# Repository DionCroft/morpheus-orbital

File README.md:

# Morpheus ORBITAL

**A six-layer KiCad prototype for a portable 7.3-inch colour e-paper device.**

Morpheus ORBITAL connects an Espressif **ESP32-S3-WROOM-1-N16R8** to a Good Display **GDEP073E01** colour e-paper panel. It adds USB-C, microSD, a Bosch **BME690** environmental sensor, and a single-cell battery power path. The board keeps the USB-C port, card slot and buttons along the edges and reserves space for the display flex and the module antenna.

[Download the prototype ZIP](https://github.com/DionCroft/morpheus-orbital/releases/download/v0.1.0-prototype/Morpheus-ORBITAL-v0.1.0-prototype.zip) · [Download the 18-sheet schematic PDF](docs/Morpheus-Schematic.pdf) · [Open in KiCad](#open-in-kicad) · [Find a component](#component-index) · [Download BOM CSV](Morpheus-BOM.csv) · [Populated STEP](docs/Morpheus-assembled.step) · [JLCPCB and bring-up checklist](docs/PROTOTYPE_CHECKLIST.md)

<p align="center">
  
</p>

*Component side shown upright. The USB-C port and microSD socket are on the left, and the display FPC is along the bottom.*

## Hardware at a glance

| Function | Main components |
| --- | --- |
| Compute and wireless | Espressif **ESP32-S3-WROOM-1-N16R8** |
| Display | Good Display **GDEP073E01** 7.3-inch colour e-paper panel and Hirose **FH34SRJ-50S-0.5SH(50)** 50-pin display connector |
| Environmental sensing | Bosch Sensortec **BME690** gas, humidity, pressure and temperature sensor |
| USB-C and protection | GCT **USB4085-GF-A**, onsemi **FUSB303BTMX** Type-C controller, and TI **TPD4E1U06DCKR** ESD protection |
| Storage | Hirose **DM3AT-SF-PEJM5** microSD socket |
| Battery and regulation | TI **BQ25616RTWR** charger, **BQ27441DRZR-G1A** fuel gauge, and **TPS63020DSJR** buck-boost converter |
| Temperature monitoring and controls | TI **ADS1115IDGSR** ADC, external thermistor headers, and **K2-1102SP-A4SC-04** boot and refresh switches |

## Open in KiCad

1. Install [KiCad 10](https://www.kicad.org/download/), including its standard libraries. The project was reviewed with KiCad **10.0.4**. Install the standard KiCad 3D model library for the complete assembly view.
2. Clone the repository below, or use [Download ZIP](https://github.com/DionCroft/morpheus-orbital/archive/refs/heads/main.zip) and extract the entire archive. The project uses relative library and model paths.

       git clone https://github.com/DionCroft/morpheus-orbital.git

3. From KiCad's project manager, open [circuit_design/Morpheus/Morpheus.kicad_pro](circuit_design/Morpheus/Morpheus.kicad_pro). Open **Schematic Editor** or **PCB Editor** from the project.
4. In PCB Editor, choose **View > 3D Viewer** to inspect the populated board. The display panel, battery, and external probes are separate from the PCB assembly.

## Mechanical model

The [populated STEP assembly](docs/Morpheus-assembled.step) contains the board and all **164 fitted components**. It is intended for CAD viewing and enclosure planning. Some component bodies use drawing-based envelopes, so check final fit against the actual mating parts.

## Rear 3D view

<p align="center">
  
</p>

## Component index

Every distinct manufacturer part number in the [reference BOM](Morpheus-BOM.csv) is listed below. The **61 part numbers** cover **169 schematic references**, including the off-board display and four DNP (do not populate) positions. The routed PCB has 164 fitted components. NT901 is the copper net tie.

### Processing, power and semiconductors

| Exact part number | Component or value | Manufacturer | References |
| --- | --- | --- | --- |
| `ADS1115IDGSR` | ADS1115 16-bit ADC | Texas Instruments | U702 |
| `BME690` | Gas, humidity, pressure and temperature sensor | Bosch Sensortec | U3 |
| `BQ25616RTWR` | BQ25616 single-cell battery charger with power path | Texas Instruments | U901 |
| `BQ27441DRZR-G1A` | BQ27441-G1A battery fuel gauge | Texas Instruments | U701 |
| `BZT52C27` | 27 V Zener diode | Jiangsu Changjing Electronics Technology | D3 |
| `ESP32-S3-WROOM-1-N16R8` | ESP32-S3 Wi-Fi and Bluetooth LE MCU module | Espressif Systems | U1 |
| `FUSB303BTMX` | FUSB303B USB Type-C port controller | onsemi | U802 |
| `KT-0805G` | Green indicator LED | Hubei KENTO Electronics | D4, D5 |
| `MBR0530T1G` | Schottky rectifier | onsemi | D2, D6, D7, D8 |
| `SI2301CDS` | P-channel MOSFET | TECH PUBLIC | Q9 |
| `SN74HCS08PWR` | Quad Schmitt-trigger AND gate | Texas Instruments | U1603 |
| `SN74LVC1G14DBVR` | Single Schmitt-trigger inverter | Texas Instruments | U803, U1601, U1602 |
| `Si1308EDL-T1-GE3` | N-channel MOSFET | Vishay | Q8 |
| `TPD4E1U06DCKR` | TPD4E1U06 four-channel ESD protection | Texas Instruments | D1 |
| `TPS2553DBVR` | TPS2553 current-limited power switch | Texas Instruments | U805 |
| `TPS389001DSET` | TPS3890 adjustable voltage supervisor | Texas Instruments | U1701 |
| `TPS389030DSET` | TPS3890 fixed-threshold voltage supervisor | Texas Instruments | U804, U806 |
| `TPS63020DSJR` | TPS63020 buck-boost converter | Texas Instruments | U807 |
| `TPS70933DBVR` | TPS70933 3.3 V LDO regulator | Texas Instruments | U801 |

### Display, connectors and switches

| Exact part number | Component or value | Manufacturer | References |
| --- | --- | --- | --- |
| `2.0-2P WT` | Two-position 2.0 mm battery connector | SHOU HAN | J2 |
| `DM3AT-SF-PEJM5` | microSD card socket | Hirose Electric | J4 |
| `FH34SRJ-50S-0.5SH(50)` | 50-position 0.5 mm display FPC connector | Hirose | J3 |
| `GDEP073E01` | 7.3-inch colour e-paper panel | Good Display | U5 (off-board) |
| `K2-1102SP-A4SC-04` | Boot and refresh tactile switch | Korean Hroparts Electronics | SW1, SW2 |
| `M20-9990246` | 2.54 mm header for temperature sense or charge disable | Harwin | J602, J603, J702 |
| `USB4085-GF-A` | USB-C receptacle | GCT | J1 |

### Capacitors and inductors

| Exact part number | Component or value | Manufacturer | References |
| --- | --- | --- | --- |
| `CL10B104KB8NNNC` | 100nF ceramic capacitor | Samsung Electro-Mechanics | C21, C22, C32, C34, C52, C54, C59, C61, C64, C69, C703, C704, C803, C804, C805, C808, C811, C1601, C1602, C1603, C1701 |
| `CL10B473KB8NNNC` | 47nF/50V ceramic capacitor | Samsung Electro-Mechanics | C904 |
| `CL21B105KBFNNNE` | 1uF ceramic capacitor | Samsung Electro-Mechanics | C23, C24, C33, C41, C42, C43, C44, C45, C46, C47 (DNP), C53, C701, C801, C806, C901 |
| `CL21B224KBFNNNE` | 220nF/50V ceramic capacitor | Samsung Electro-Mechanics | C816, C817 |
| `CL21B474KBFNNNE` | 470nF/50V ceramic capacitor | Samsung Electro-Mechanics | C55, C68, C702 |
| `CL31B225KBHNNNE` | 2.2uF/50V ceramic capacitor | Samsung Electro-Mechanics | C40 |
| `CL31B475KBHNNNE` | 4.7uF/50V ceramic capacitor | Samsung Electro-Mechanics | C56, C62, C67, C802, C903 |
| `CL32B106KBJNNNE` | 10uF ceramic capacitor | Samsung Electro-Mechanics | C31, C35, C48, C49, C50, C51, C57, C58, C60, C63, C65, C66, C807, C809, C810, C902, C905, C906, C907, C908 |
| `CL32B226KAJNNNE` | 22uF/25V ceramic capacitor | Samsung Electro-Mechanics | C812, C813, C814 |
| `GRM1555C1H102JA01D` | 1nF/50V ceramic capacitor (C0G) | Murata | C90 |
| `LQH32PN100MNCL` | 10 uH inductor | Murata | L3, L4 |
| `XAL5030-102MEC` | 1 uH power inductor | Coilcraft | L901 |
| `XGL4020-152MEC` | 1.5 uH power inductor | Coilcraft | L801 |

### Resistors and current sense

| Exact part number | Component or value | Manufacturer | References |
| --- | --- | --- | --- |
| `CRF1206-FZ-R010ELF` | 10 mOhm current-sense resistor | Bourns | R701 |
| `CRM1206-FX-R220ELF` | 0.22 Ohm current-sense resistor | Bourns | R28, R30 |
| `ERA3AEB1022V` | 10.2k resistor | Panasonic Industry | R1702 |
| `ERA3AEB184V` | 180k resistor | Panasonic Industry | R811 |
| `ERA3AEB303V` | 30k resistor | Panasonic Industry | R1701 |
| `RC0603FR-07100KL` | 100k resistor | Yageo | R24 (DNP), R1703 |
| `RC0603FR-0710KL` | 10k resistor | Yageo | R12, R13, R21, R605, R702, R703, R706, R708, R709, R802, R813, R814, R815, R902, R1001, R1002, R1003, R1004, R1005 |
| `RC0603FR-071K5L` | 1.5k resistor | Yageo | R901 |
| `RC0603FR-071KL` | 1k resistor | Yageo | R707 |
| `RC0603FR-071ML` | 1M resistor | Yageo | R27, R29, R704, R705, R809 |
| `RC0603FR-0722KL` | 22k resistor | Yageo | R806 |
| `RC0603FR-07249KL` | 249k resistor | Yageo | R805 |
| `RC0603FR-072K2L` | 2.2k resistor | Yageo | R710, R711, R1006, R1007 |
| `RC0603FR-07300KL` | 300k resistor | Yageo | R804 |
| `RC0603FR-0746K4L` | 46.4k resistor | Yageo | R602 |
| `RC0603FR-07470KL` | 470k resistor | Yageo | R808 |
| `RC0603FR-0747KL` | 47k resistor | Yageo | R23 (DNP) |
| `RC0603FR-07510RL` | 510 Ohm resistor | Yageo | R14, R15, R903 |
| `RC0603FR-075K9L` | 5.9k resistor | Yageo | R601 |
| `RC0603JR-070RL` | 0R jumper resistor | Yageo | R25, R26, R31 (DNP), R32, R33, R34, R801 |
| `RC1206FR-07220RL` | 220R resistor | Yageo | R812 |
| `RT0603BRD071ML` | 1M resistor | Yageo | R810 |

## Prototype and reuse

Use the [JLCPCB ordering and first-board bring-up checklist](docs/PROTOTYPE_CHECKLIST.md) to plan a prototype order and record the bench results.

This is a reviewed CAD prototype. The full PCB DRC recorded zero unconnected items, three warnings and 50 reviewed footprint-parity records. Hardware qualification is open for USB impedance on the finished stackup, selective filled and capped vias, display bias and startup, battery and thermistor behaviour, display connector fit, RF performance, and assembly clearances. Verify those items against the actual parts and fabrication process before building.

The original hardware design is licensed under [CERN-OHL-S-2.0](LICENSES/CERN-OHL-S-2.0.txt). The source location is [this repository](https://github.com/DionCroft/morpheus-orbital). The crest artwork and personal signature retain separate terms. KiCad library material retains its upstream license. [Third-party and artwork notices](THIRD_PARTY_NOTICES.md).

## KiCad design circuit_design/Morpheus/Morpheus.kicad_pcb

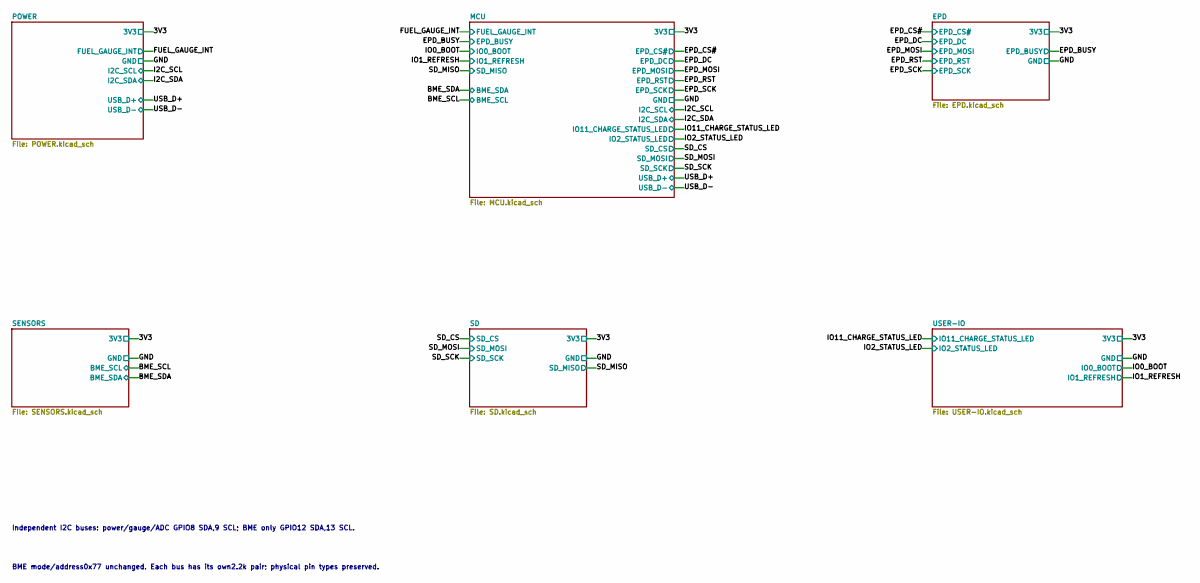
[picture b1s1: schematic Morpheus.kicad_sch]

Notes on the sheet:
Independent I2C buses: power/gauge/ADC GPIO8 SDA,9 SCL; BME only GPIO12 SDA,13 SCL.
BME mode/address0x77 unchanged. Each bus has its own2.2k pair; physical pin types preserved.

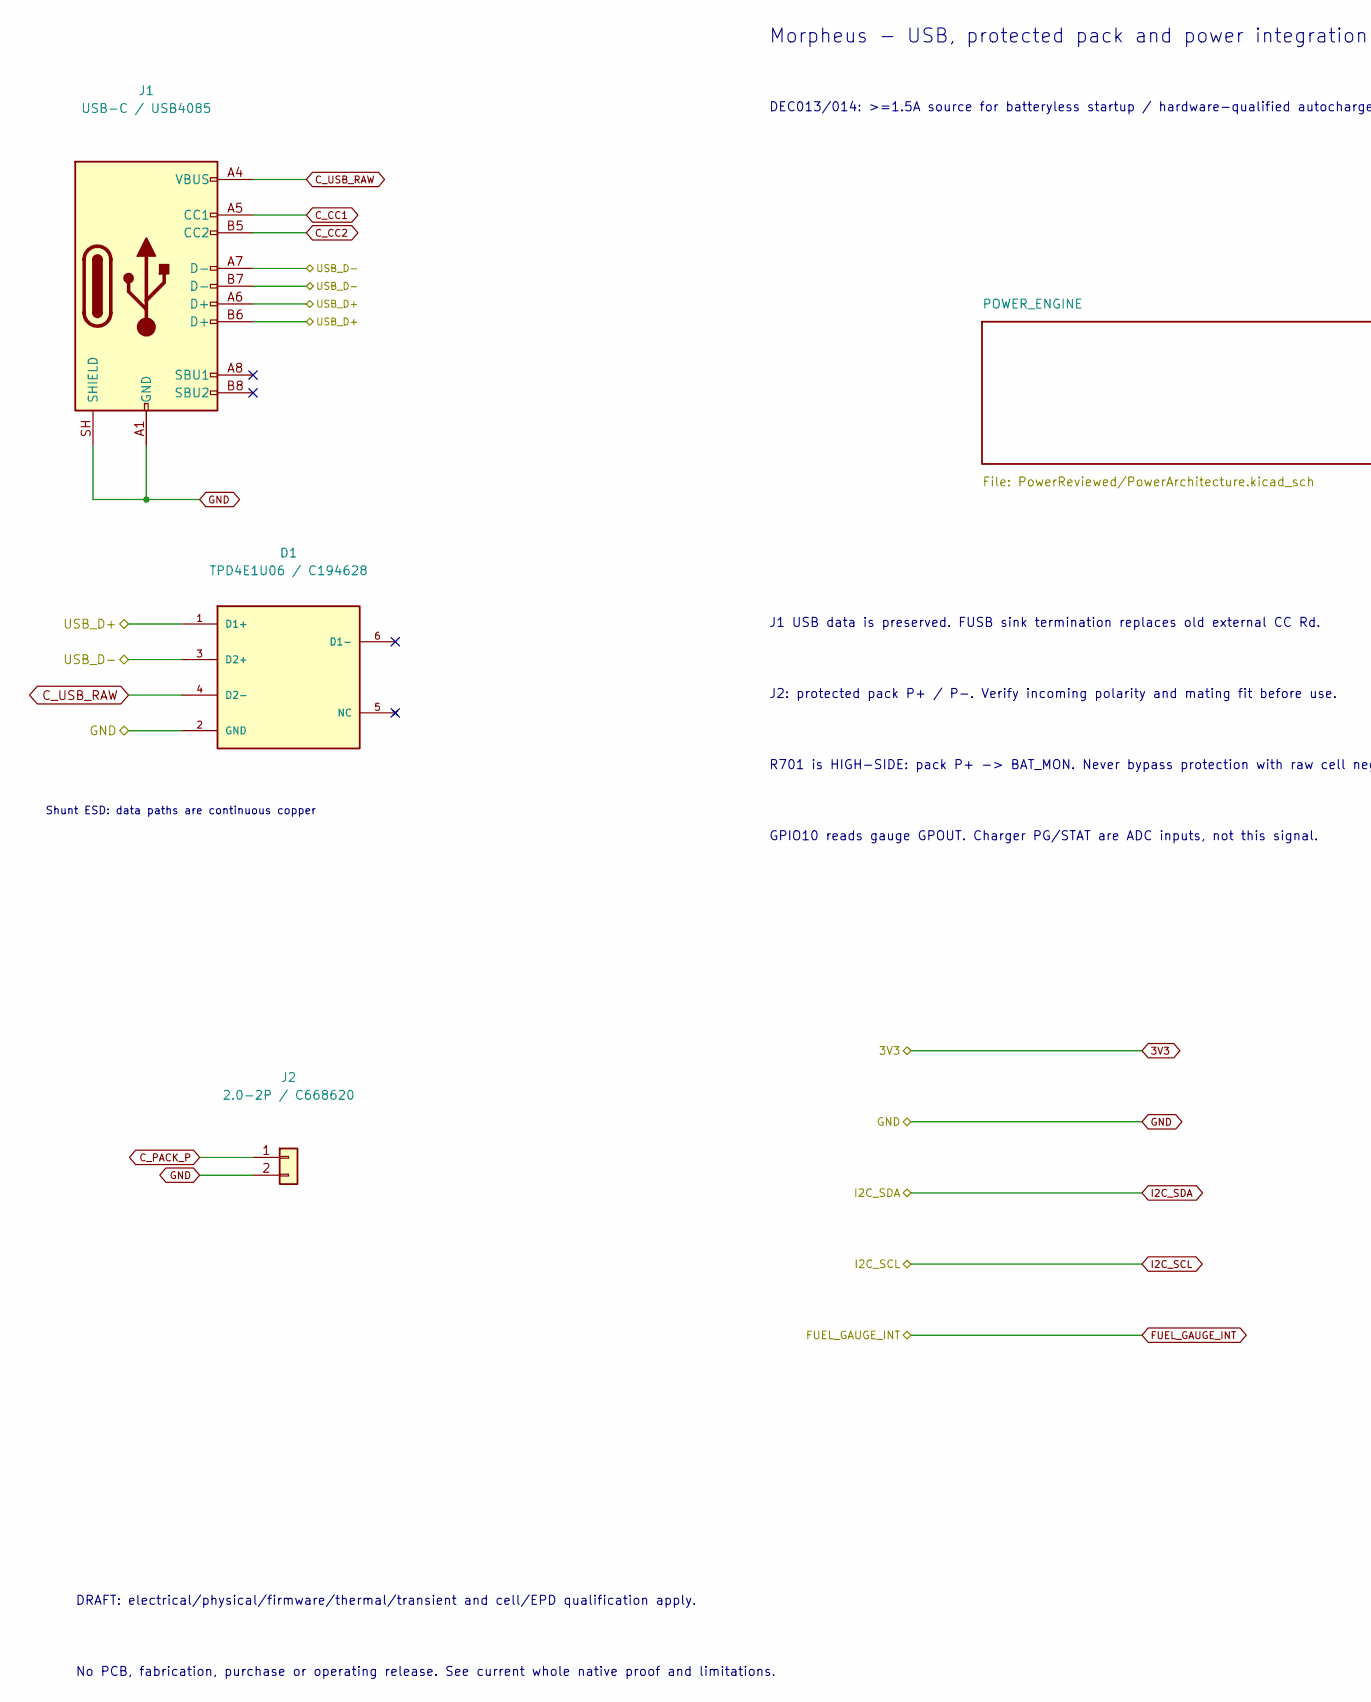
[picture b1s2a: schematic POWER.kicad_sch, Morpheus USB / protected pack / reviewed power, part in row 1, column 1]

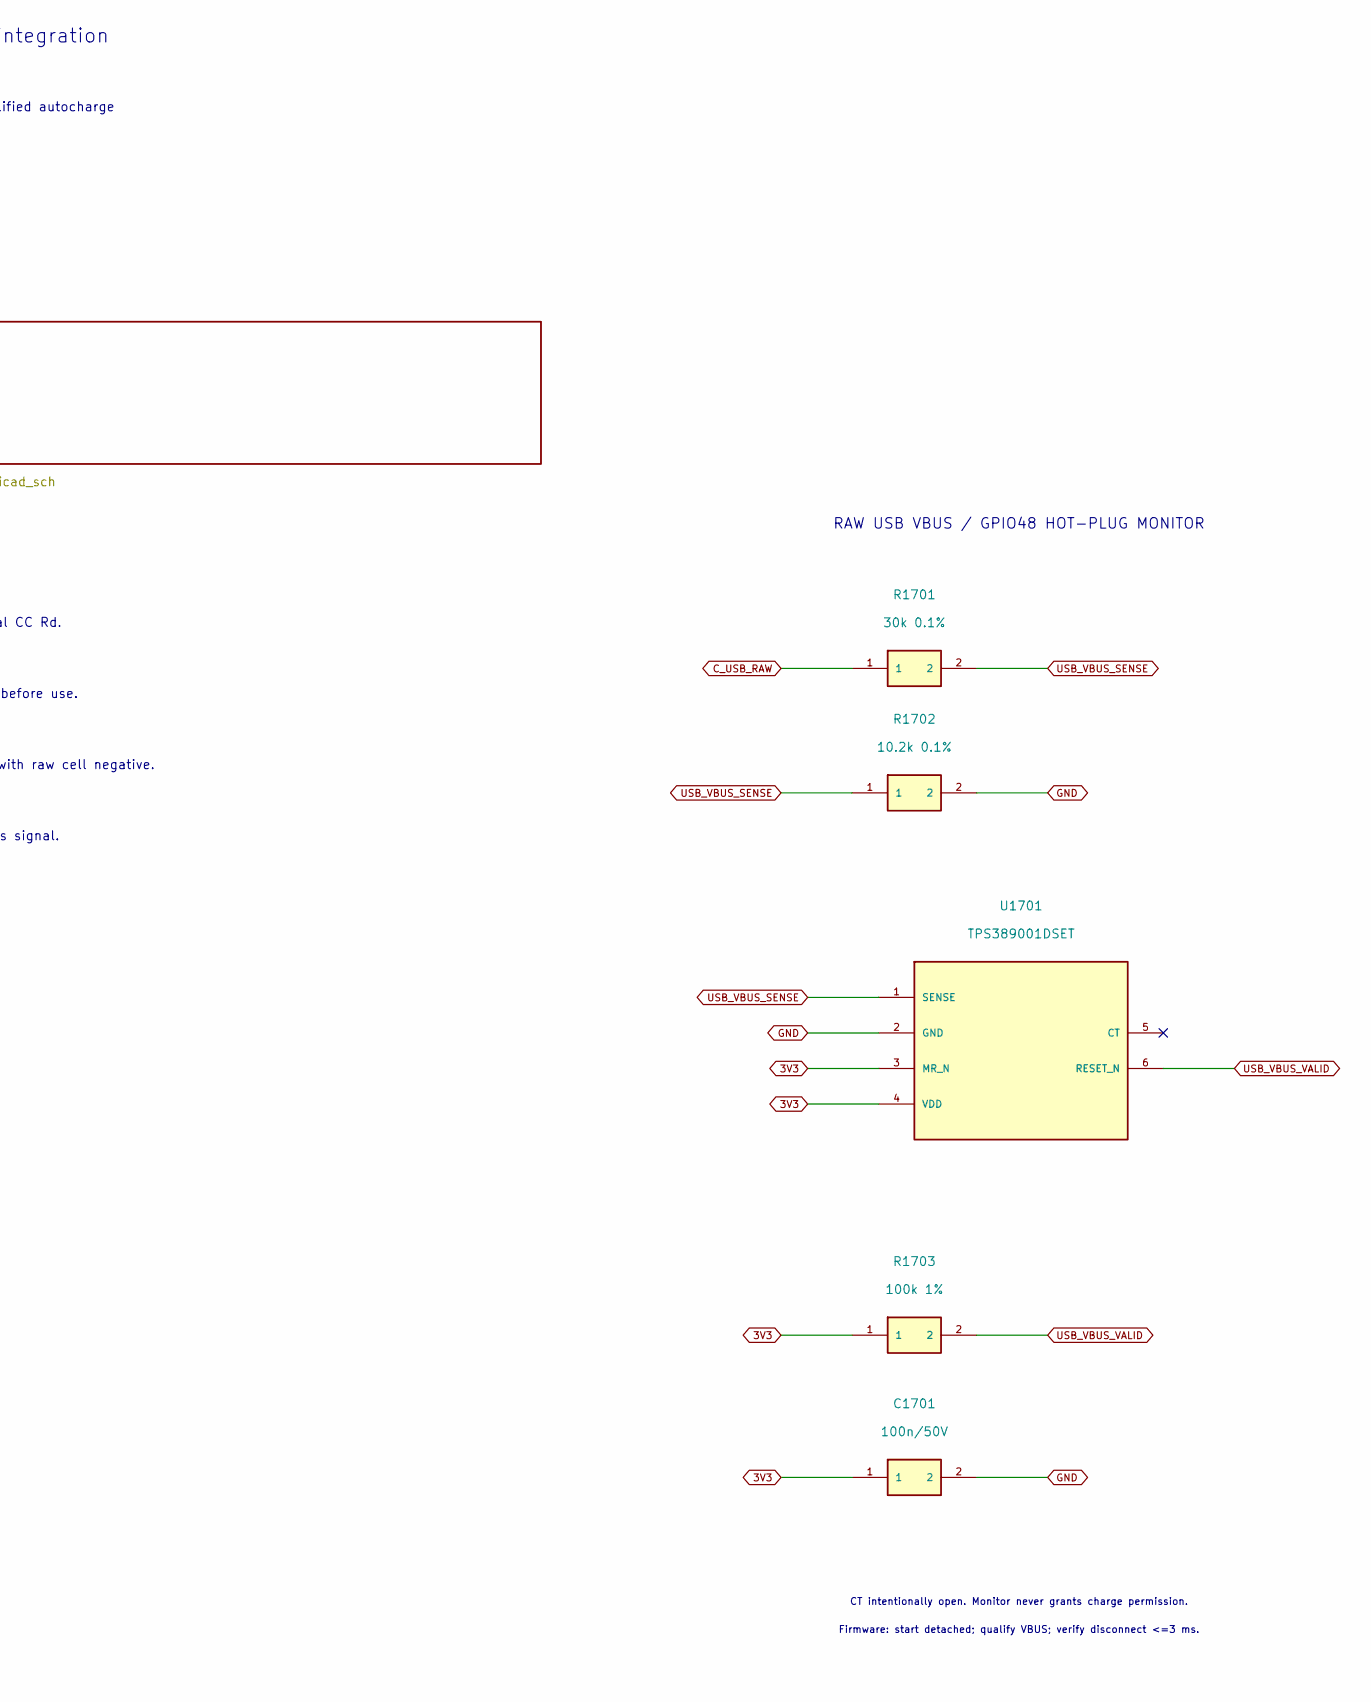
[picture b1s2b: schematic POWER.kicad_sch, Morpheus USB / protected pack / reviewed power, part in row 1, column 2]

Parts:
C1701: 100n/50V; Samsung_C0603; ManufacturerPartNumber CL10B104KB8NNNC
D1: TPD4E1U06 / C194628; TI_TPD4E1U06_DCK0006A; ManufacturerPartNumber TPD4E1U06DCKR; LCSC C194628
J1: USB-C / USB4085; USB_C_Receptacle_GCT_USB4085_GF_A; ManufacturerPartNumber USB4085-GF-A
J2: 2.0-2P / C668620; SHOU_HAN_2_0_2P_WT; ManufacturerPartNumber 2.0-2P WT; LCSC C668620
R1701: 30k 0.1%; Panasonic_ERA3A; ManufacturerPartNumber ERA3AEB303V
R1702: 10.2k 0.1%; Panasonic_ERA3A; ManufacturerPartNumber ERA3AEB1022V
R1703: 100k 1%; R_0603_1608Metric; ManufacturerPartNumber RC0603FR-07100KL
U1701: TPS389001DSET; TI_DSE0006A; ManufacturerPartNumber TPS389001DSET

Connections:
3V3: C1701.1, R1703.1, U1701.3 (MR_N), U1701.4 (VDD); also elsewhere on the board
/USB_D+: D1.1 (D1+), J1.A6 (D+), J1.B6 (D+); also elsewhere on the board
/USB_D-: D1.3 (D2+), J1.A7 (D-), J1.B7 (D-); also elsewhere on the board
C_CC1: J1.A5 (CC1); also elsewhere on the board
C_CC2: J1.B5 (CC2); also elsewhere on the board
C_PACK_P: J2.1; also elsewhere on the board
C_USB_RAW: D1.4 (D2-), J1.A4 (VBUS), J1.A9 (VBUS), J1.B4 (VBUS), J1.B9 (VBUS), R1701.1; also elsewhere on the board
GND: C1701.2, D1.2 (GND), J1.A1 (GND), J1.A12 (GND), J1.B1 (GND), J1.B12 (GND), J1.SH (SHIELD), J2.2, R1702.2, U1701.2 (GND); also elsewhere on the board
USB_VBUS_SENSE: R1701.2, R1702.1, U1701.1 (SENSE)
USB_VBUS_VALID: R1703.2, U1701.6 (RESET_N); also elsewhere on the board

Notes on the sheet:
Shunt ESD: data paths are continuous copper
Morpheus - USB, protected pack and power integration
DEC013/014: >=1.5A source for batteryless startup / hardware-qualified autocharge
J1 USB data is preserved. FUSB sink termination replaces old external CC Rd.
J2: protected pack P+ / P-. Verify incoming polarity and mating fit before use.
R701 is HIGH-SIDE: pack P+ -> BAT_MON. Never bypass protection with raw cell negative.
GPIO10 reads gauge GPOUT. Charger PG/STAT are ADC inputs, not this signal.
DRAFT: electrical/physical/firmware/thermal/transient and cell/EPD qualification apply.
No PCB, fabrication, purchase or operating release. See current whole native proof and limitations.
RAW USB VBUS / GPIO48 HOT-PLUG MONITOR
CT intentionally open. Monitor never grants charge permission.
Firmware: start detached; qualify VBUS; verify disconnect <=3 ms.

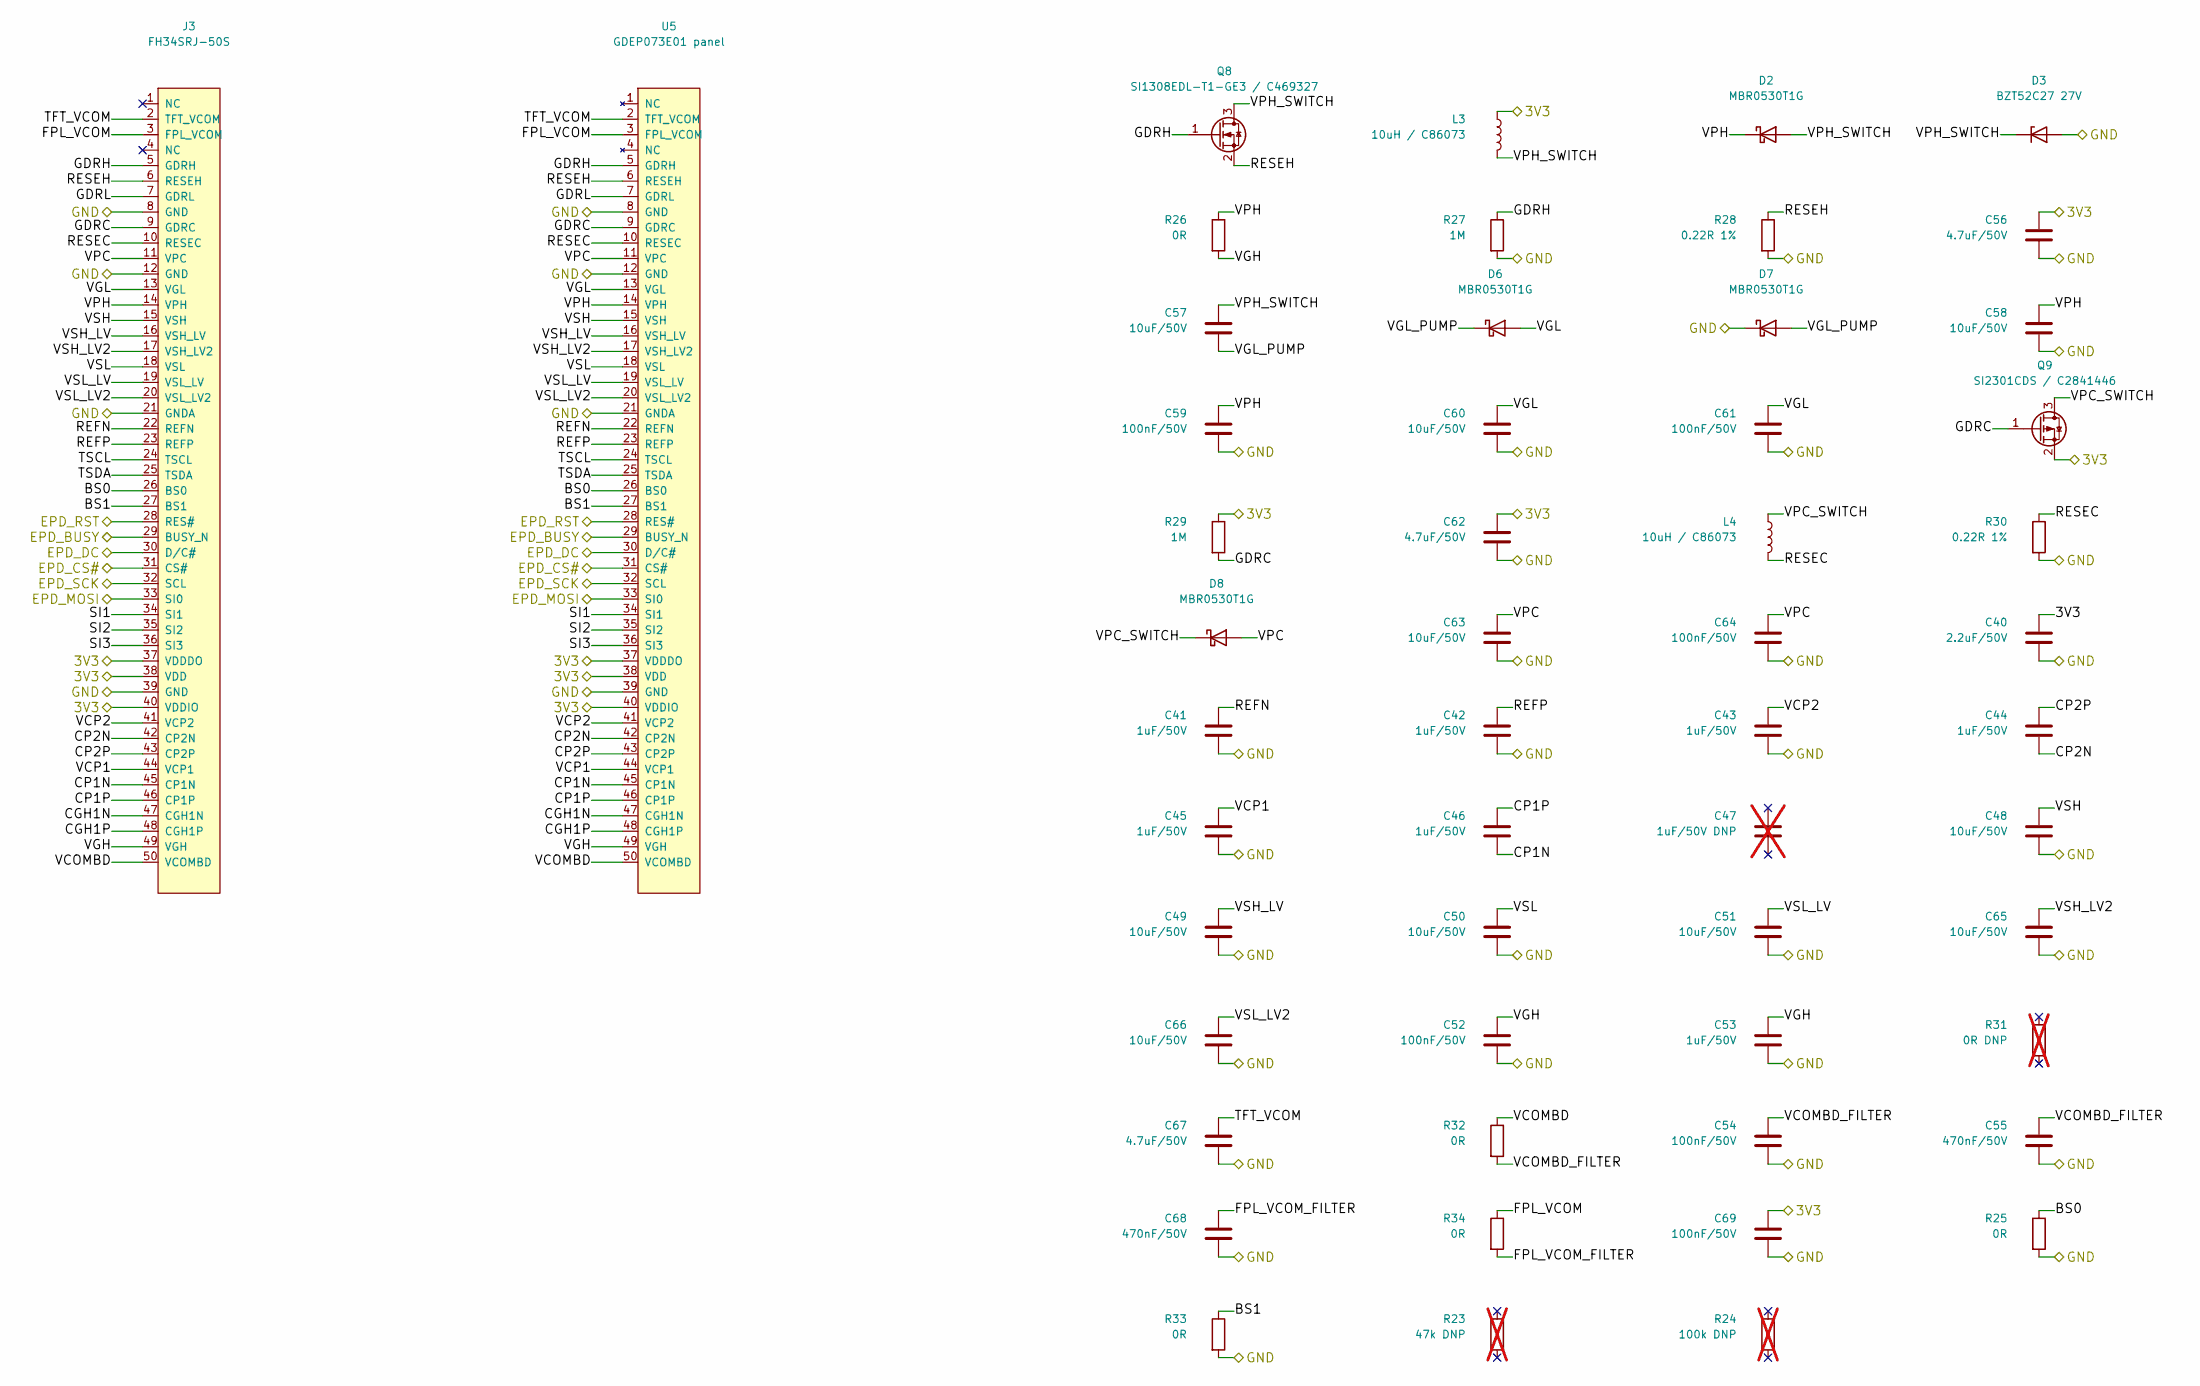
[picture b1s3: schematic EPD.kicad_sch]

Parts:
C40: 2.2uF/50V; Samsung_C1206; ManufacturerPartNumber CL31B225KBHNNNE
C41, C42, C43, C44, C45, C46, C53: 1uF/50V; Samsung_C0805; ManufacturerPartNumber CL21B105KBFNNNE
C47: 1uF/50V DNP; Samsung_C0805; ManufacturerPartNumber CL21B105KBFNNNE; not fitted
C48, C49, C50, C51, C57, C58, C60, C63, C65, C66: 10uF/50V; Samsung_C1210; ManufacturerPartNumber CL32B106KBJNNNE; LCSC C138687
C52, C54, C59, C61, C64, C69: 100nF/50V; Samsung_C0603; ManufacturerPartNumber CL10B104KB8NNNC
C55, C68: 470nF/50V; Samsung_C0805; ManufacturerPartNumber CL21B474KBFNNNE
C56, C62, C67: 4.7uF/50V; Samsung_C1206; ManufacturerPartNumber CL31B475KBHNNNE
D2, D6, D7, D8: MBR0530T1G; onsemi_MBR0530_SOD123; ManufacturerPartNumber MBR0530T1G; LCSC C82046
D3: BZT52C27 27V; JSCJ_BZT52C_SOD123; ManufacturerPartNumber BZT52C27; LCSC C81935
J3: FH34SRJ-50S; Hirose_FH34SRJ_50S_0_5SH_50_Primary; ManufacturerPartNumber FH34SRJ-50S-0.5SH(50)
L3, L4: 10uH / C86073; L_Murata_LQH32PN100MNCL; ManufacturerPartNumber LQH32PN100MNCL; LCSC C86073
Q8: SI1308EDL-T1-GE3 / C469327; SOT323_Vishay_Si1308EDL; ManufacturerPartNumber Si1308EDL-T1-GE3; LCSC C469327
Q9: SI2301CDS / C2841446; TECH_PUBLIC_SI2301CDS_Physical_GSD; ManufacturerPartNumber SI2301CDS; LCSC C2841446
R23: 47k DNP; R_0603_1608Metric; ManufacturerPartNumber RC0603FR-0747KL; not fitted
R24: 100k DNP; R_0603_1608Metric; ManufacturerPartNumber RC0603FR-07100KL; not fitted
R25, R26, R32, R33, R34: 0R; R_0603_1608Metric; ManufacturerPartNumber RC0603JR-070RL
R27, R29: 1M; R_0603_1608Metric; ManufacturerPartNumber RC0603FR-071ML
R28, R30: 0.22R 1%; Bourns_CRM1206; ManufacturerPartNumber CRM1206-FX-R220ELF
R31: 0R DNP; R_0603_1608Metric; ManufacturerPartNumber RC0603JR-070RL; not fitted
U5: GDEP073E01 panel; ManufacturerPartNumber GDEP073E01

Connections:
3V3: C40.1, C56.1, C62.1, C69.1, J3.37 (VDDDO), J3.38 (VDD), J3.40 (VDDIO), L3.1, Q9.2 (S), R29.1, U5.37 (VDDDO), U5.38 (VDD), U5.40 (VDDIO); also elsewhere on the board
/EPD/BS0: J3.26 (BS0), R25.1, U5.26 (BS0)
/EPD/BS1: J3.27 (BS1), R33.1, U5.27 (BS1)
/EPD/CGH1N: J3.47 (CGH1N), U5.47 (CGH1N)
/EPD/CGH1P: J3.48 (CGH1P), U5.48 (CGH1P)
/EPD/CP1N: C46.2, J3.45 (CP1N), U5.45 (CP1N)
/EPD/CP1P: C46.1, J3.46 (CP1P), U5.46 (CP1P)
/EPD/CP2N: C44.2, J3.42 (CP2N), U5.42 (CP2N)
/EPD/CP2P: C44.1, J3.43 (CP2P), U5.43 (CP2P)
/EPD/FPL_VCOM: J3.3 (FPL_VCOM), R34.1, U5.3 (FPL_VCOM)
/EPD/FPL_VCOM_FILTER: C68.1, R34.2
/EPD/GDRC: J3.9 (GDRC), Q9.1 (G), R29.2, U5.9 (GDRC)
/EPD/GDRH: J3.5 (GDRH), Q8.1 (G), R27.1, U5.5 (GDRH)
/EPD/GDRL: J3.7 (GDRL), U5.7 (GDRL)
/EPD/REFN: C41.1, J3.22 (REFN), U5.22 (REFN)
/EPD/REFP: C42.1, J3.23 (REFP), U5.23 (REFP)
/EPD/RESEC: J3.10 (RESEC), L4.2, R30.1, U5.10 (RESEC)
/EPD/RESEH: J3.6 (RESEH), Q8.2 (S), R28.1, U5.6 (RESEH)
/EPD/SI1: J3.34 (SI1), U5.34 (SI1)
/EPD/SI2: J3.35 (SI2), U5.35 (SI2)
/EPD/SI3: J3.36 (SI3), U5.36 (SI3)
/EPD/TFT_VCOM: C67.1, J3.2 (TFT_VCOM), U5.2 (TFT_VCOM)
/EPD/TSCL: J3.24 (TSCL), U5.24 (TSCL)
/EPD/TSDA: J3.25 (TSDA), U5.25 (TSDA)
/EPD/VCOMBD: J3.50 (VCOMBD), R32.1, U5.50 (VCOMBD)
/EPD/VCOMBD_FILTER: C54.1, C55.1, R32.2
/EPD/VCP1: C45.1, J3.44 (VCP1), U5.44 (VCP1)
/EPD/VCP2: C43.1, J3.41 (VCP2), U5.41 (VCP2)
/EPD/VGH: C52.1, C53.1, J3.49 (VGH), R26.2, U5.49 (VGH)
/EPD/VGL: C60.1, C61.1, D6.2 (A), J3.13 (VGL), U5.13 (VGL)
/EPD/VGL_PUMP: C57.2, D6.1 (K), D7.2 (A)
/EPD/VPC: C63.1, C64.1, D8.2 (A), J3.11 (VPC), U5.11 (VPC)
/EPD/VPC_SWITCH: D8.1 (K), L4.1, Q9.3 (D)
/EPD/VPH: C58.1, C59.1, D2.1 (K), J3.14 (VPH), R26.1, U5.14 (VPH)
/EPD/VPH_SWITCH: C57.1, D2.2 (A), D3.1 (K), L3.2, Q8.3 (D)
/EPD/VSH: C48.1, J3.15 (VSH), U5.15 (VSH)
/EPD/VSH_LV: C49.1, J3.16 (VSH_LV), U5.16 (VSH_LV)
/EPD/VSH_LV2: C65.1, J3.17 (VSH_LV2), U5.17 (VSH_LV2)
/EPD/VSL: C50.1, J3.18 (VSL), U5.18 (VSL)
/EPD/VSL_LV: C51.1, J3.19 (VSL_LV), U5.19 (VSL_LV)
/EPD/VSL_LV2: C66.1, J3.20 (VSL_LV2), U5.20 (VSL_LV2)
/EPD_BUSY: J3.29 (BUSY_N), U5.29 (BUSY_N); also elsewhere on the board
/EPD_CS#: J3.31 (CS#), U5.31 (CS#); also elsewhere on the board
/EPD_DC: J3.30 (D/C#), U5.30 (D/C#); also elsewhere on the board
/EPD_MOSI: J3.33 (SI0), U5.33 (SI0); also elsewhere on the board
/EPD_RST: J3.28 (RES#), U5.28 (RES#); also elsewhere on the board
/EPD_SCK: J3.32 (SCL), U5.32 (SCL); also elsewhere on the board
GND: C40.2, C41.2, C42.2, C43.2, C45.2, C48.2, C49.2, C50.2, C51.2, C52.2, C53.2, C54.2, C55.2, C56.2, C58.2, C59.2, C60.2, C61.2, C62.2, C63.2, C64.2, C65.2, C66.2, C67.2, C68.2, C69.2, D3.2 (A), D7.1 (K), J3.8 (GND), J3.12 (GND), J3.21 (GNDA), J3.39 (GND), R25.2, R27.2, R28.2, R30.2, R33.2, U5.8 (GND), U5.12 (GND), U5.21 (GNDA), U5.39 (GND); also elsewhere on the board

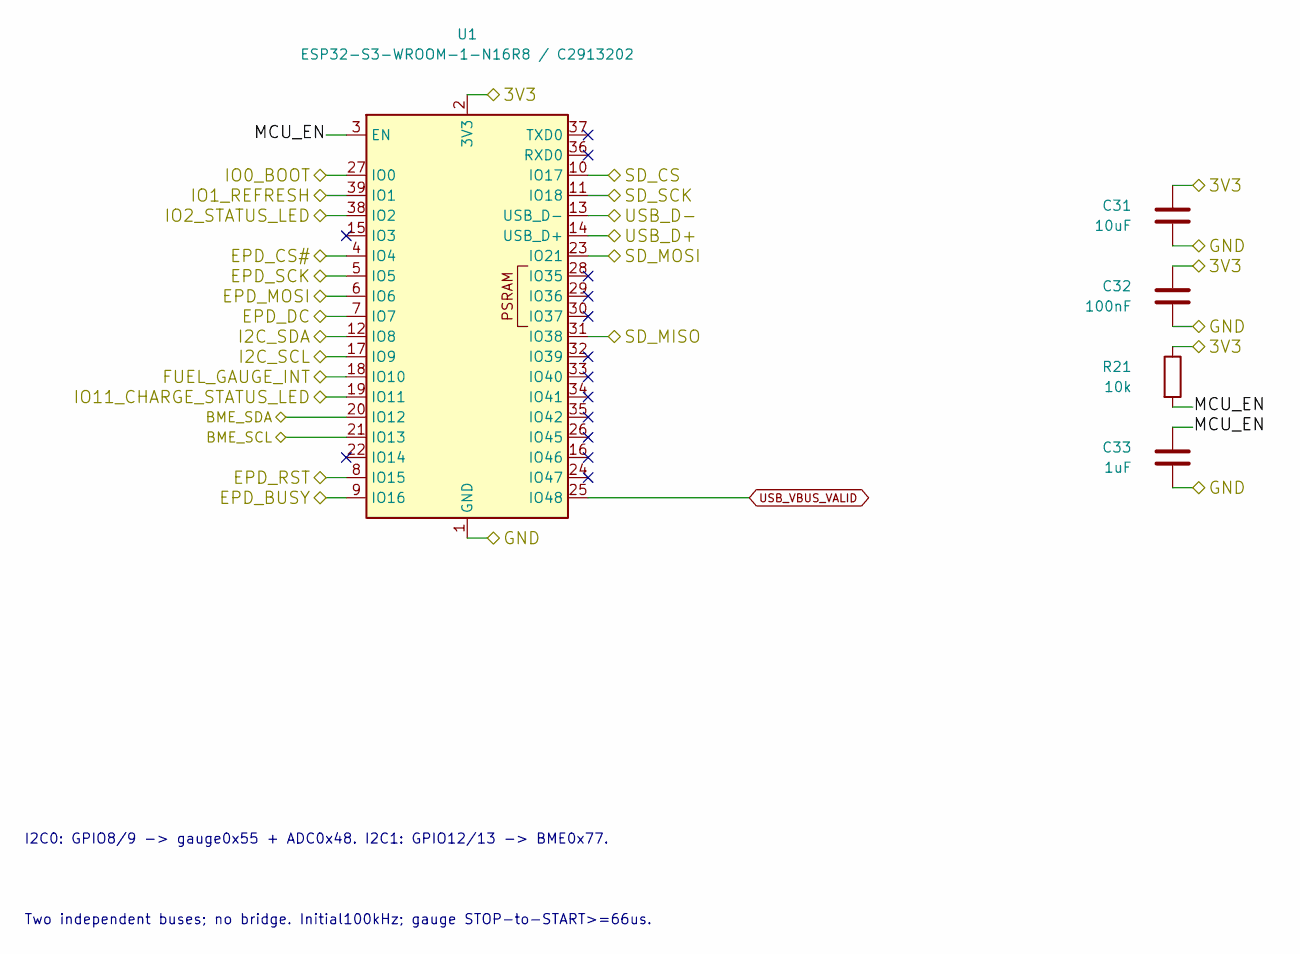
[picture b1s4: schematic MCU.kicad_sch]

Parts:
C31: 10uF; Samsung_C1210; ManufacturerPartNumber CL32B106KBJNNNE; LCSC C138687
C32: 100nF; Samsung_C0603; ManufacturerPartNumber CL10B104KB8NNNC
C33: 1uF; Samsung_C0805; ManufacturerPartNumber CL21B105KBFNNNE
R21: 10k; R_0603_1608Metric; ManufacturerPartNumber RC0603FR-0710KL
U1: ESP32-S3-WROOM-1-N16R8 / C2913202; ESP32_S3_WROOM1_Primary_9EP; ManufacturerPartNumber ESP32-S3-WROOM-1-N16R8; LCSC C2913202

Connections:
3V3: C31.1, C32.1, R21.1, U1.2 (3V3); also elsewhere on the board
/BME_SCL: U1.21 (IO13); also elsewhere on the board
/BME_SDA: U1.20 (IO12); also elsewhere on the board
/EPD_BUSY: U1.9 (IO16); also elsewhere on the board
/EPD_CS#: U1.4 (IO4); also elsewhere on the board
/EPD_DC: U1.7 (IO7); also elsewhere on the board
/EPD_MOSI: U1.6 (IO6); also elsewhere on the board
/EPD_RST: U1.8 (IO15); also elsewhere on the board
/EPD_SCK: U1.5 (IO5); also elsewhere on the board
/IO0_BOOT: U1.27 (IO0); also elsewhere on the board
/IO1_REFRESH: U1.39 (IO1); also elsewhere on the board
/IO2_STATUS_LED: U1.38 (IO2); also elsewhere on the board
/IO11_CHARGE_STATUS_LED: U1.19 (IO11); also elsewhere on the board
/MCU/MCU_EN: C33.1, R21.2, U1.3 (EN)
/SD_CS: U1.10 (IO17); also elsewhere on the board
/SD_MISO: U1.31 (IO38); also elsewhere on the board
/SD_MOSI: U1.23 (IO21); also elsewhere on the board
/SD_SCK: U1.11 (IO18); also elsewhere on the board
/USB_D+: U1.14 (USB_D+); also elsewhere on the board
/USB_D-: U1.13 (USB_D-); also elsewhere on the board
FUEL_GAUGE_INT: U1.18 (IO10); also elsewhere on the board
GND: C31.2, C32.2, C33.2, U1.1 (GND), U1.40 (GND), U1.41 (GND); also elsewhere on the board
I2C_SCL: U1.17 (IO9); also elsewhere on the board
I2C_SDA: U1.12 (IO8); also elsewhere on the board
USB_VBUS_VALID: U1.25 (IO48); also elsewhere on the board

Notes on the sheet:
I2C0: GPIO8/9 -> gauge0x55 + ADC0x48. I2C1: GPIO12/13 -> BME0x77.
Two independent buses; no bridge. Initial100kHz; gauge STOP-to-START>=66us.

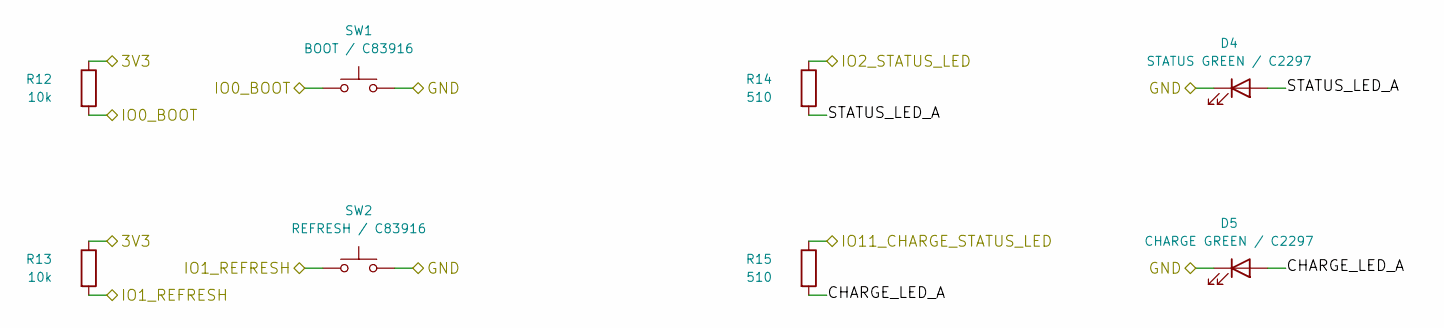
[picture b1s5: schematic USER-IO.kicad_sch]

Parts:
D4: STATUS GREEN / C2297; KENTO_KT0805G_Primary_KA; ManufacturerPartNumber KT-0805G; LCSC C2297
D5: CHARGE GREEN / C2297; KENTO_KT0805G_Primary_KA; ManufacturerPartNumber KT-0805G; LCSC C2297
R12, R13: 10k; R_0603_1608Metric; ManufacturerPartNumber RC0603FR-0710KL
R14, R15: 510; R_0603_1608Metric; ManufacturerPartNumber RC0603FR-07510RL
SW1: BOOT / C83916; HRO_K2_1102SP_A4SC_Primary; ManufacturerPartNumber K2-1102SP-A4SC-04; LCSC C83916
SW2: REFRESH / C83916; HRO_K2_1102SP_A4SC_Primary; ManufacturerPartNumber K2-1102SP-A4SC-04; LCSC C83916

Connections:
3V3: R12.1, R13.1; also elsewhere on the board
/IO0_BOOT: R12.2, SW1.1; also elsewhere on the board
/IO1_REFRESH: R13.2, SW2.1; also elsewhere on the board
/IO2_STATUS_LED: R14.1; also elsewhere on the board
/IO11_CHARGE_STATUS_LED: R15.1; also elsewhere on the board
/USER-IO/CHARGE_LED_A: D5.2 (A), R15.2
/USER-IO/STATUS_LED_A: D4.2 (A), R14.2
GND: D4.1 (K), D5.1 (K), SW1.2, SW2.2; also elsewhere on the board

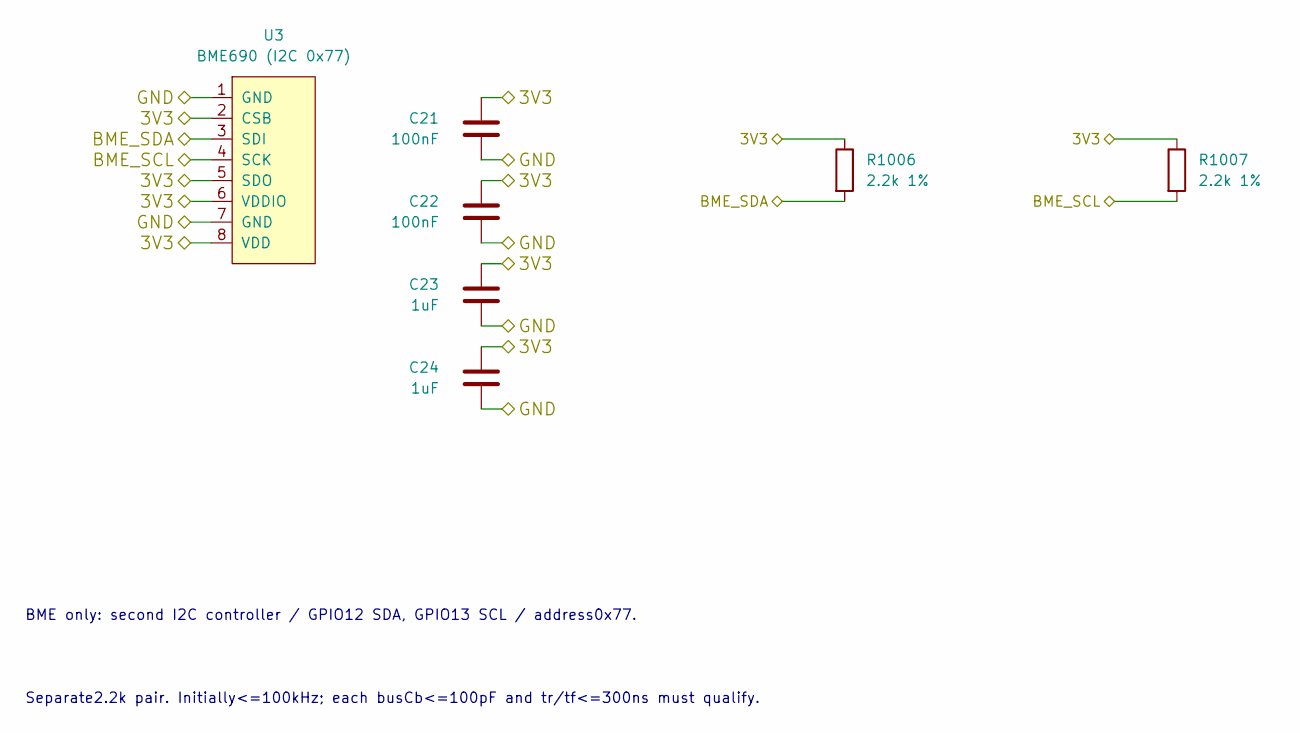
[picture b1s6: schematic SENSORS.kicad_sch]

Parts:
C21, C22: 100nF; Samsung_C0603; ManufacturerPartNumber CL10B104KB8NNNC
C23, C24: 1uF; Samsung_C0805; ManufacturerPartNumber CL21B105KBFNNNE
R1006, R1007: 2.2k 1%; R_0603_1608Metric; ManufacturerPartNumber RC0603FR-072K2L
U3: BME690 (I2C 0x77); Bosch_BME690_Primary_Top; ManufacturerPartNumber BME690; LCSC C42431867

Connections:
3V3: C21.1, C22.1, C23.1, C24.1, R1006.1, R1007.1, U3.2 (CSB), U3.5 (SDO), U3.6 (VDDIO), U3.8 (VDD); also elsewhere on the board
/BME_SCL: R1007.2, U3.4 (SCK); also elsewhere on the board
/BME_SDA: R1006.2, U3.3 (SDI); also elsewhere on the board
GND: C21.2, C22.2, C23.2, C24.2, U3.1 (GND), U3.7 (GND); also elsewhere on the board

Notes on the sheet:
BME only: second I2C controller / GPIO12 SDA, GPIO13 SCL / address0x77.
Separate2.2k pair. Initially<=100kHz; each busCb<=100pF and tr/tf<=300ns must qualify.

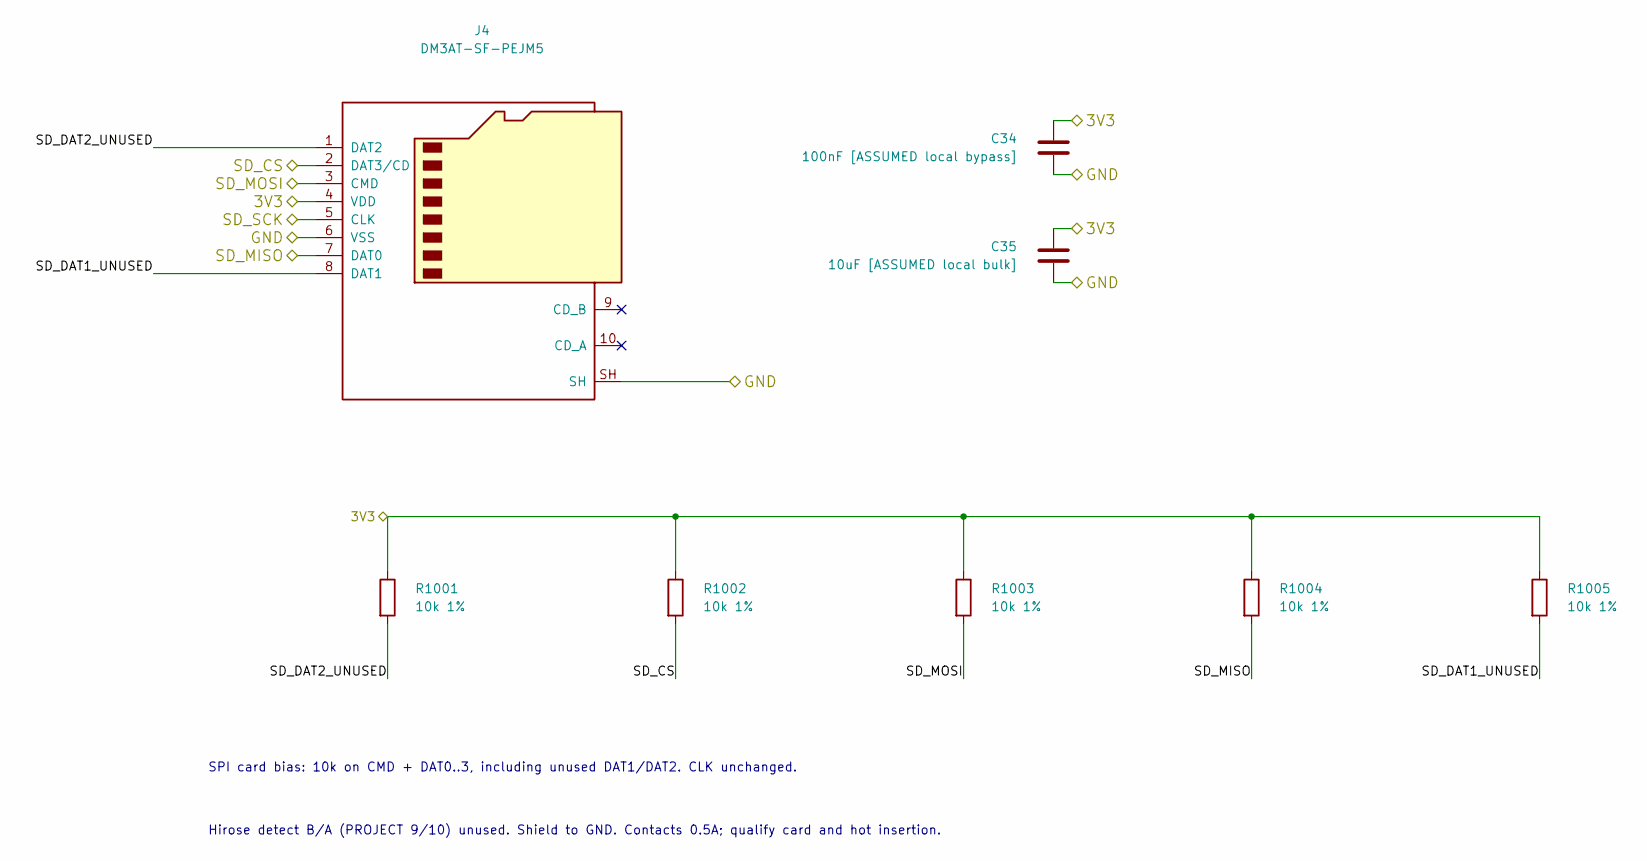
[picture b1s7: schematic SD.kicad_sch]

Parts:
C34: 100nF [ASSUMED local bypass]; Samsung_C0603; ManufacturerPartNumber CL10B104KB8NNNC
C35: 10uF [ASSUMED local bulk]; Samsung_C1210; ManufacturerPartNumber CL32B106KBJNNNE; LCSC C138687
J4: DM3AT-SF-PEJM5; microSD_Hirose_DM3AT_Primary; ManufacturerPartNumber DM3AT-SF-PEJM5
R1001, R1002, R1003, R1004, R1005: 10k 1%; R_0603_1608Metric; ManufacturerPartNumber RC0603FR-0710KL; LCSC C98220

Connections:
3V3: C34.1, C35.1, J4.4 (VDD), R1001.1, R1002.1, R1003.1, R1004.1, R1005.1; also elsewhere on the board
/SD/SD_DAT1_UNUSED: J4.8 (DAT1), R1005.2
/SD/SD_DAT2_UNUSED: J4.1 (DAT2), R1001.2
/SD_CS: J4.2 (DAT3/CD), R1002.2; also elsewhere on the board
/SD_MISO: J4.7 (DAT0), R1004.2; also elsewhere on the board
/SD_MOSI: J4.3 (CMD), R1003.2; also elsewhere on the board
/SD_SCK: J4.5 (CLK); also elsewhere on the board
GND: C34.2, C35.2, J4.6 (VSS), J4.SH; also elsewhere on the board

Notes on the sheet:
SPI card bias: 10k on CMD + DAT0..3, including unused DAT1/DAT2. CLK unchanged.
Hirose detect B/A (PROJECT 9/10) unused. Shield to GND. Contacts 0.5A; qualify card and hot insertion.
